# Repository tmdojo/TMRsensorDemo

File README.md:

# TMR Sensor Demo

This repo contains demo board and code for TDK TMR Angle Sensor
https://product.tdk.com/info/en/products/sensor/angle/tmr-angle/index.html

Important Note!
In v1.1 27-Apr-2017 board, Pin#1 ADDR of ADC1x15 is routed to GPIO #11 of Feather. Set this pin to LOW or HIGH for proper operation.
TMRsensorDemo.ino has been updated to accomodate this.

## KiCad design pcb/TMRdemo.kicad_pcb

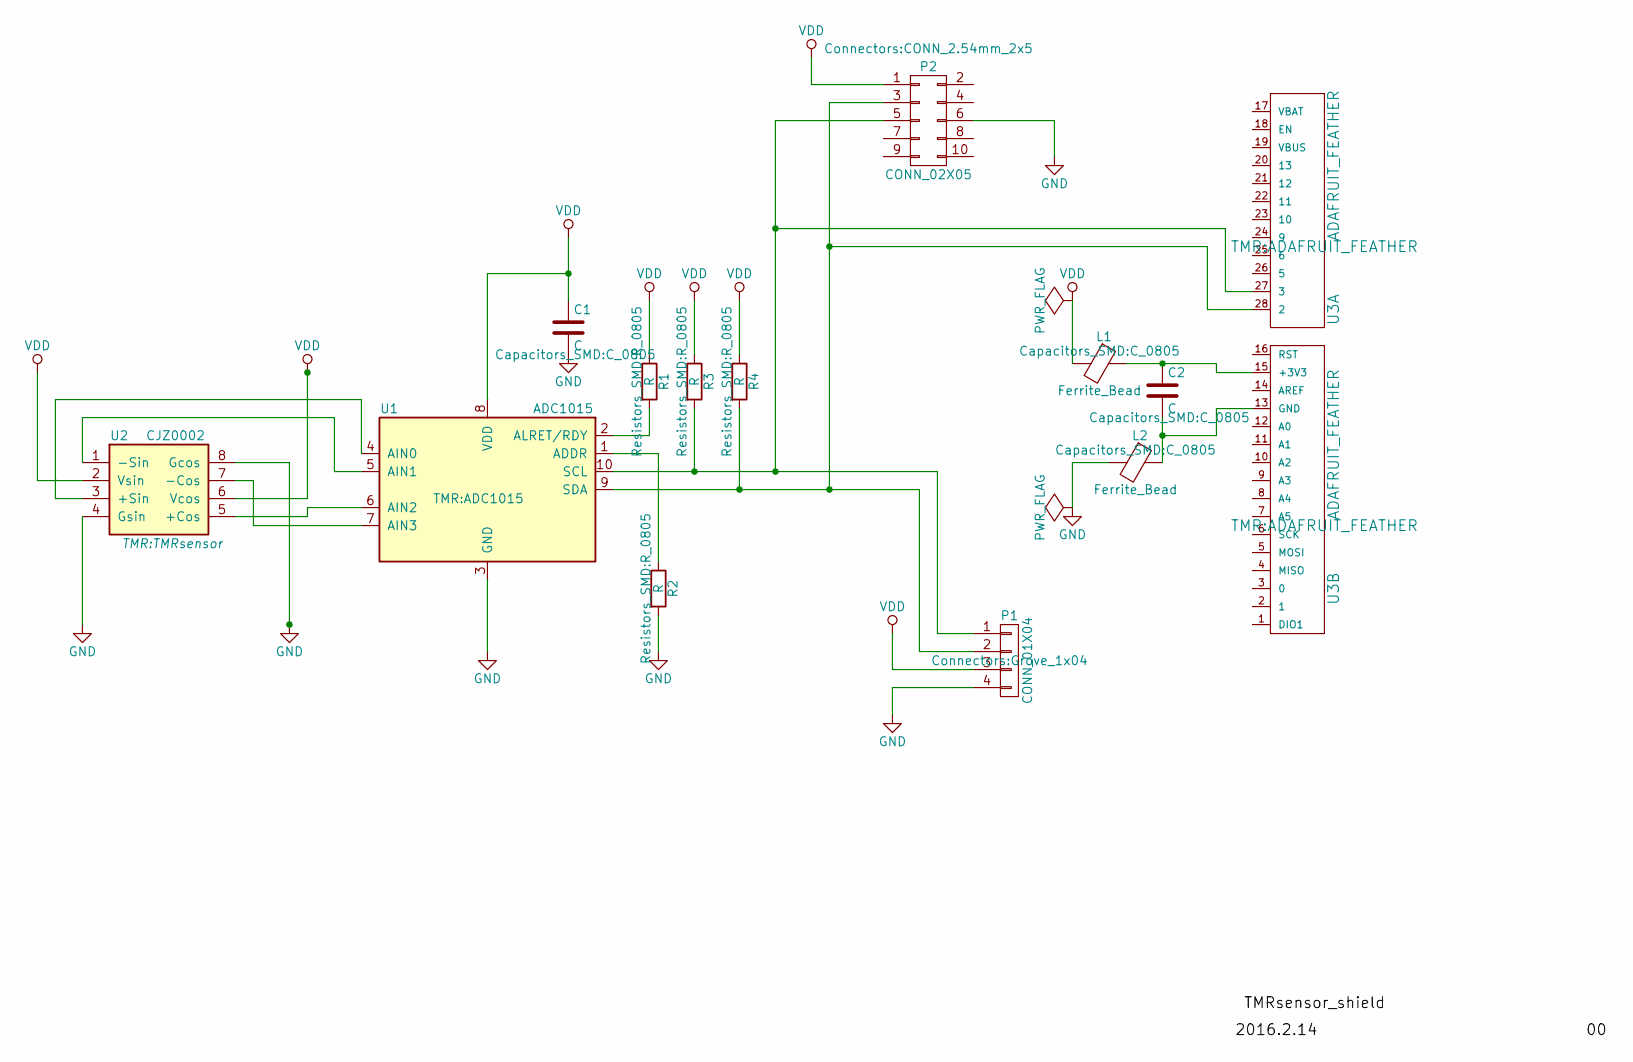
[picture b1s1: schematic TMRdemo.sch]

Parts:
C1, C2: C; C_0805
L1, L2: Ferrite_Bead; C_0805
P1: CONN_01X04; Grove_1x04
P2: CONN_02X05; CONN_2.54mm_2x5
R1, R2, R3, R4: R; R_0805
U1: ADC1015
U2: CJZ0002; TMRsensor
U3: ADAFRUIT_FEATHER

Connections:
GND: C1.2, L2.2, P1.4, P2.6, R2.2, U1.3 (GND), U2.4 (Gsin), U2.8 (Gcos)
unnamed: C2.1, L1.1, U3.15 (+3V3)
unnamed: C2.2, L2.1, U3.13 (GND)
unnamed: P1.1, P2.5, R3.2, U1.10 (SCL), U3.27 (3)
unnamed: P1.2, P2.3, R4.2, U1.9 (SDA), U3.28 (2)
unnamed: R1.2, U1.2 (ALRET/RDY)
unnamed: R2.1, U1.1 (ADDR)
unnamed: U1.4 (AIN0), U2.3 (+Sin)
unnamed: U1.5 (AIN1), U2.1 (-Sin)
unnamed: U1.6 (AIN2), U2.5 (+Cos)
unnamed: U1.7 (AIN3), U2.7 (-Cos)
VDD: C1.1, L1.2, P1.3, P2.1, R1.1, R3.1, R4.1, U1.8 (VDD), U2.2 (Vsin), U2.6 (Vcos)

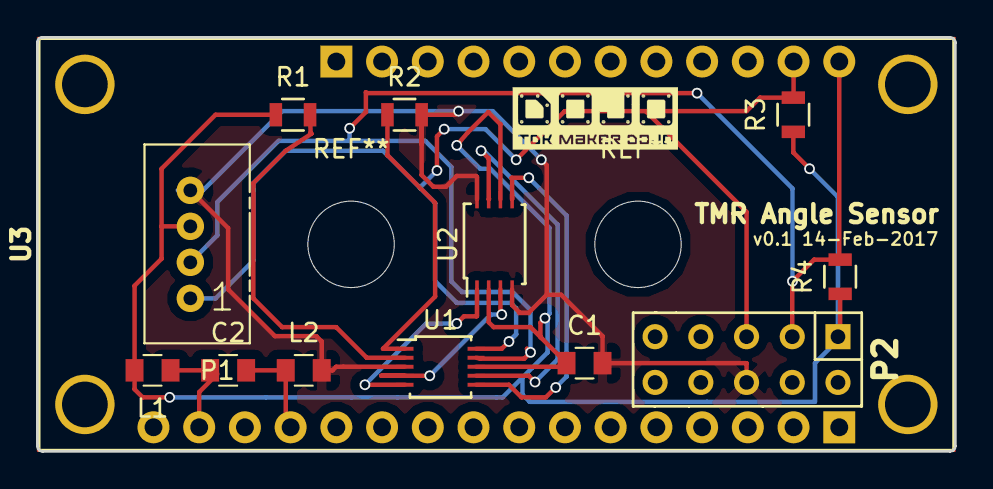
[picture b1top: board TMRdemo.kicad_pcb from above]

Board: 2 copper layers, 51.0 x 23.0 mm, 13 parts (0 on the bottom side), 12 nets.

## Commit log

2017-10-19 Add KiCad PCB
2017-12-24 Add pdf
2018-01-12 Amend README and .ino for v1.1 board. Board data is not updated.
